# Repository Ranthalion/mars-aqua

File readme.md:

View this project on [CADLAB.io](https://cadlab.io/project/1833). 

# Mars Aqua Adapter
Adds support for pwm based dimming for Mars Aqua LED lights

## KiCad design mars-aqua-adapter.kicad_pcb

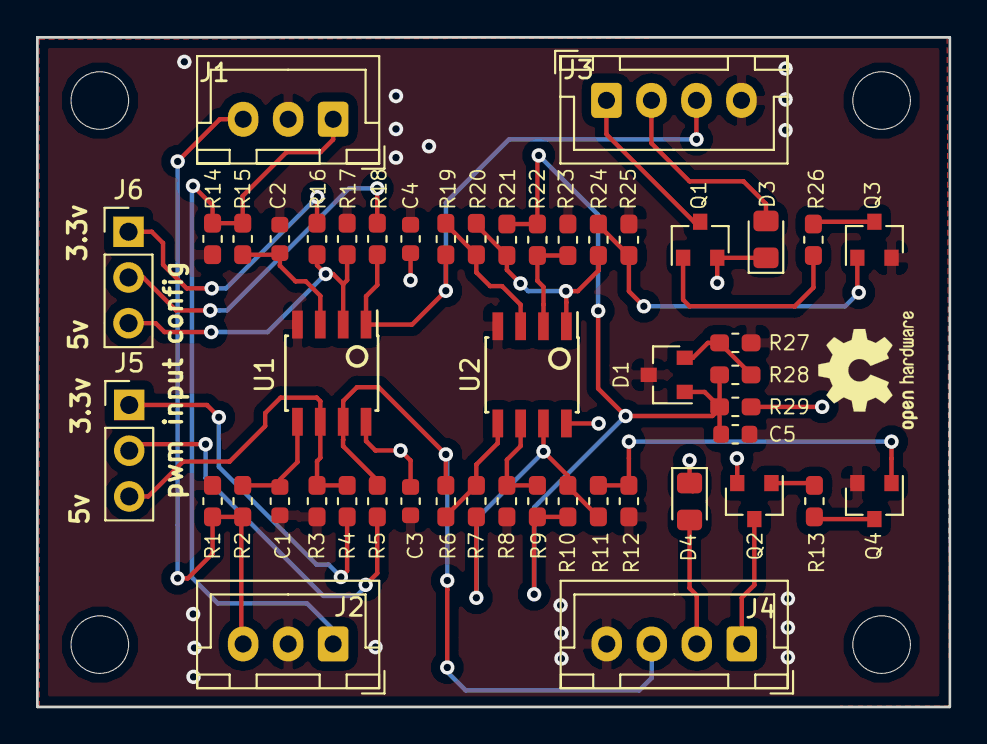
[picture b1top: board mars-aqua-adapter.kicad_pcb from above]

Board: 2 copper layers, 50.7 x 37.2 mm, 49 parts (0 on the bottom side), 32 nets.

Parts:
C1, C2: 4.7uF; C_0603_1608Metric
C3, C4: 0.1uF; C_0603_1608Metric
C5: 10nF; C_0603_1608Metric
D1: TL431DBZ; SOT-23
D3, D4: D_Schottky; D_0805_2012Metric_Pad1.15x1.40mm_HandSolder
J1, J2: Conn_01x03; JST_XH_B03B-XH-A_1x03_P2.50mm_Vertical
J3, J4: Conn_01x04; JST_XH_B04B-XH-A_1x04_P2.50mm_Vertical
J5, J6: Conn_01x03; PinHeader_1x03_P2.54mm_Vertical
Q1, Q2: Q_PNP_BEC; SOT-23
Q3, Q4: Q_NPN_BEC; SOT-23
R1, R9, R14, R22: 330k; R_0603_1608Metric_Pad1.05x0.95mm_HandSolder
R2, R15: 20k; R_0603_1608Metric_Pad1.05x0.95mm_HandSolder
R3, R4, R5, R6, R11, R13, R16, R17, R18, R19, R24, R26, R27, R28: 100k; R_0603_1608Metric_Pad1.05x0.95mm_HandSolder
R7, R12, R20, R25: 1M; R_0603_1608Metric_Pad1.05x0.95mm_HandSolder
R8, R23: 82k; R_0603_1608Metric_Pad1.05x0.95mm_HandSolder
R10, R21: 10k; R_0603_1608Metric_Pad1.05x0.95mm_HandSolder
R29: 22; R_0603_1608Metric_Pad1.05x0.95mm_HandSolder
U1: LM358; SOIC-8_3.9x4.9mm_P1.27mm
U2: LM393; SOIC-8_3.9x4.9mm_P1.27mm

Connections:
+12V: C3.1, C4.1, D3.1, D4.1, Q1.2, Q2.2, R29.1, U1.8, U2.8
/Vref: C5.1, D1.1, R9.1, R10.1, R21.1, R22.1, R28.1, R29.2
/ch1_enable: J3.1, Q1.3
/ch1_input: J1.1, J2.1, R14.1, R15.2
/ch1_output: J3.3, R18.2, R19.2, U1.1
/ch2_enable: J4.1, Q2.3
/ch2_input: J1.3, J2.3, R1.1, R2.2
/ch2_output: J4.3, R5.2, R6.2, U1.7
GND: C1.2, C2.2, C3.2, C4.2, C5.2, D1.3, J1.2, J2.2, J3.4, J4.4, Q3.2, Q4.2, R1.2, R3.2, R8.2, R12.1, R14.2, R17.2, R23.2, R25.1, R27.2, U1.4, U2.4
unnamed: C1.1, R2.1, U1.5
unnamed: C2.1, R15.1, U1.3
unnamed: D1.2, R27.1, R28.2
unnamed: D3.2, J3.2
unnamed: D4.2, J4.2
unnamed: J5.1, R4.1
unnamed: J5.2, R5.1
unnamed: J5.3, R3.1, R4.2, U1.6
unnamed: J6.1, R16.1
unnamed: J6.2, R18.1
unnamed: J6.3, R16.2, R17.1, U1.2
unnamed: Q1.1, R26.2
unnamed: Q2.1, R13.2
unnamed: Q3.1, R24.2, R25.2
unnamed: Q3.3, R26.1
unnamed: Q4.1, R11.2, R12.2
unnamed: Q4.3, R13.1
unnamed: R6.1, R7.2, U2.5
unnamed: R8.1, R9.2, U2.6
unnamed: R7.1, R10.2, R11.1, U2.7
unnamed: R19.1, R20.2, U2.3
unnamed: R20.1, R21.2, R24.1, U2.1
unnamed: R22.2, R23.1, U2.2

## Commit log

2019-03-07 Circuit
2019-03-08 board layout
2019-03-09 Final Layout
2019-05-22 Fix traces on comparator
2019-05-22 Updated schematic image and add annotated pcb
2019-05-27 Add hysteresis
2019-06-06 Backlink to CADLAB.io has been added.
2019-06-19 Add voltage reference
2019-07-13 gerber updates
2019-07-15 update feedback and regulator values
2020-04-02 Update values
2020-04-02 Update images
